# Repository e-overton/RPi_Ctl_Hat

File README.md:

Robot control pi hat
=======================

Adds buffered GPIO outputs at 5V
Adds CANbus
Adds I2C breakout pincs with protection
Adds 8-way gpio extender

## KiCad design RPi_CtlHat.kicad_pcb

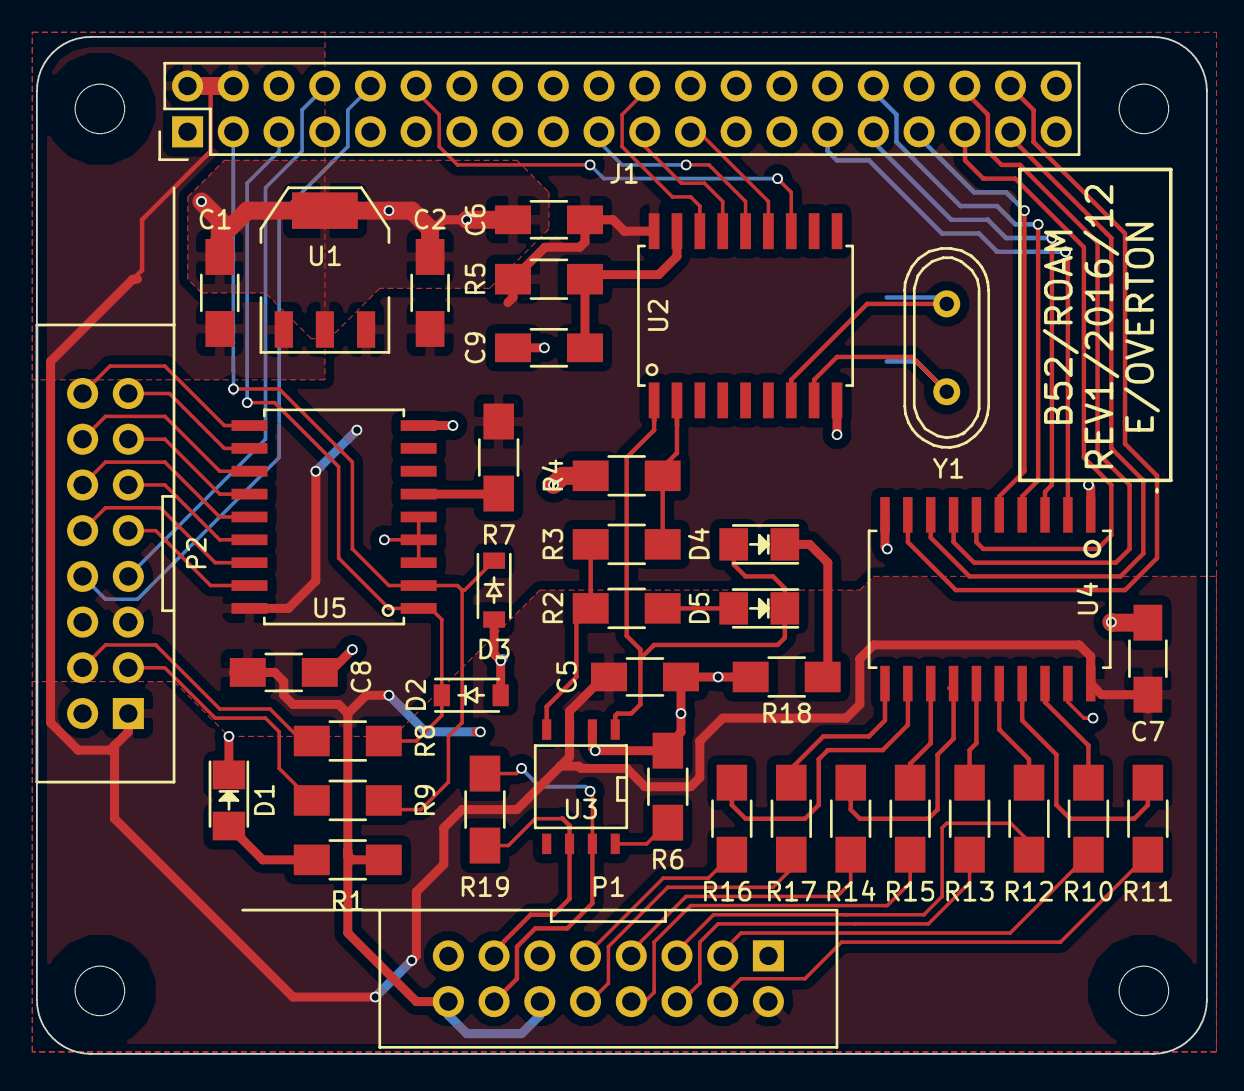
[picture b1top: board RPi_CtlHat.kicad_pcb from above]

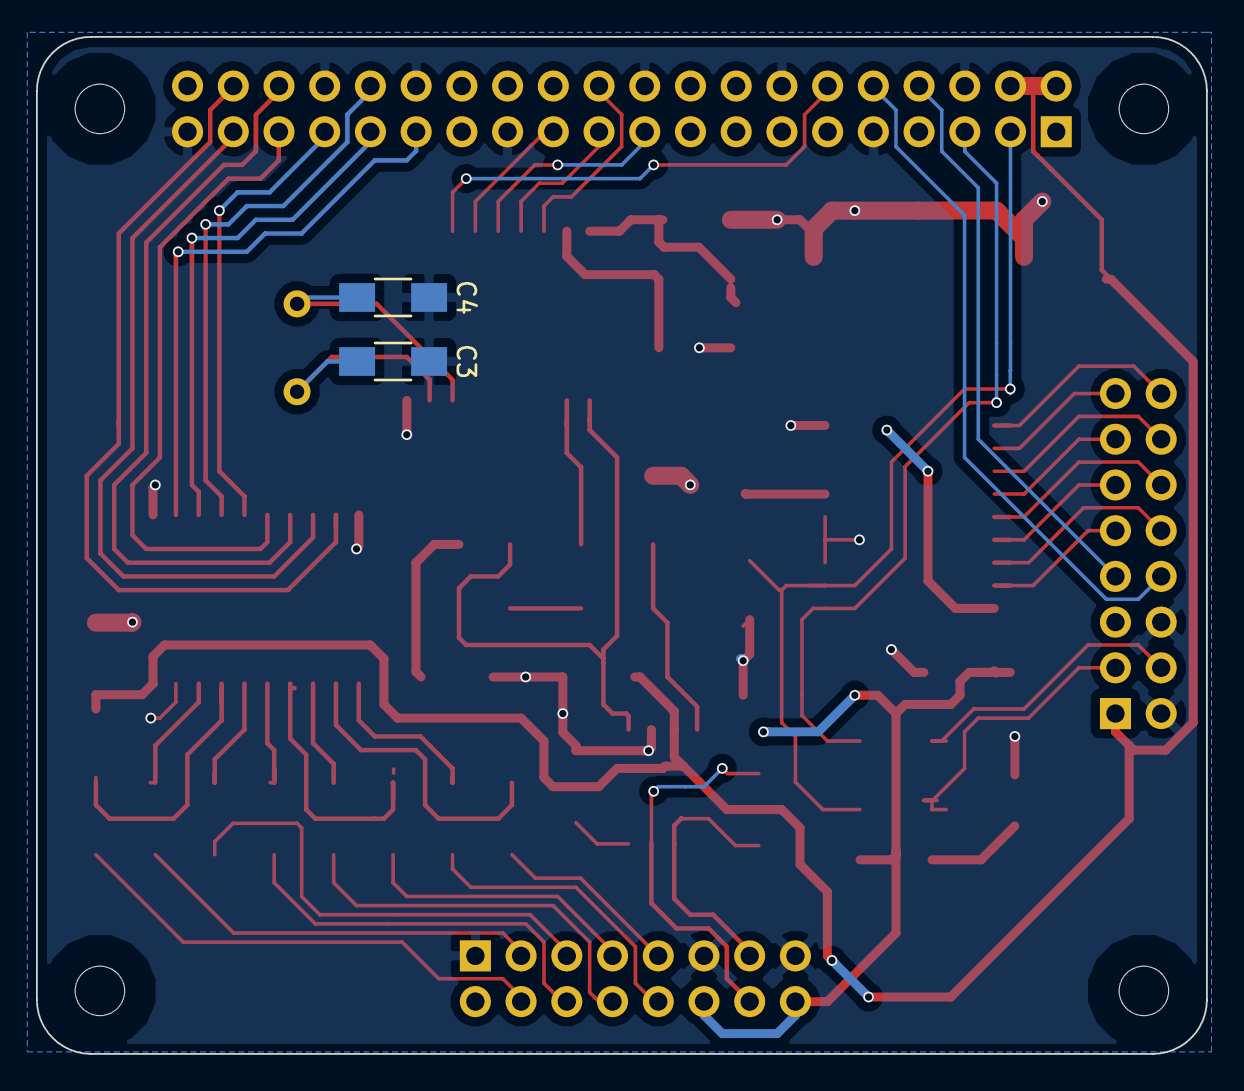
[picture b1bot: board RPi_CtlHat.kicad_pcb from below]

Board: 2 copper layers, 65.0 x 56.5 mm, 42 parts (2 on the bottom side), 59 nets.

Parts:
C1, C2: 1u; C_1206_HandSoldering
C3, C4: 22p; C_1206_HandSoldering
C5, C6, C7, C8: 100n; C_1206_HandSoldering
C9: ?n; C_1206_HandSoldering
D1, D4, D5: LED; LED_1206
D2, D3: 3.3v; SOD-123
J1: RPi_GPIO; Pin_Header_Straight_2x20
P1, P2: CONN_02X08; D300_16
R1, R8, R9, R10, R11, R12, R13, R14, R15, R16, R17: 100R; R_1206_HandSoldering
R2, R18: 200R; R_1206_HandSoldering
R3, R4, R5, R6, R7: 4k7; R_1206_HandSoldering
R19: 120R; R_1206_HandSoldering
U1: MCP1754ST-3302E/MB; SOT-223
U2: MCP2515; SOIC-18
U3: MCP2551; SOIC-8-N
U4: 74HCT541_PWR; SOIC20
U5: MCP23008; SOIC-18
Y1: 16MHz; Crystal_HC49-U_Vertical

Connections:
+5V: C1.1, C5.1, C7.1, J1.2, J1.4, P1.2, P2.1, U1.1, U3.3, U4.20
/CAN0_CE: J1.22, U2.16
/CAN0_INT: J1.12, U2.12
/CAN0_RXCAN: R3.2, R4.1, U2.2
/CAN0_TXCAN: D4.2, D5.1, U2.1, U3.1
/CANH: P1.14, R19.2, U3.7
/CANL: P1.13, R19.1, U3.6
/GPIO14TX: J1.8, P2.7
/GPIO15RX: J1.10, P2.8
/PWM0: J1.29, U4.2
/PWM0_OUT: P1.3, R10.1
/PWM1: J1.31, U4.3
/PWM1_OUT: P1.4, R11.1
/PWM2: J1.32, U4.4
/PWM2_OUT: P1.5, R12.1
/PWM3: J1.33, U4.5
/PWM3_OUT: P1.6, R13.1
/PWM4: J1.35, U4.6
/PWM4_OUT: P1.7, R14.1
/PWM5: J1.36, U4.7
/PWM5_OUT: P1.8, R15.1
/PWM6: J1.37, U4.8
/PWM6_OUT: P1.9, R16.1
/PWM7: J1.38, U4.9
/PWM7_OUT: P1.10, R17.1
/SCL1: D2.1, J1.5, R8.2, U5.1
/SCL1B: P2.4, R8.1
/SDA1: D3.1, J1.3, R9.2, U5.2
/SDA1B: P2.3, R9.1
/SPI0_CLK: J1.23, U2.13
/SPI0_MISO: J1.21, U2.15
/SPI0_MOSI: J1.19, U2.14
/XGPIO0: P2.16, U5.10
/XGPIO1: P2.15, U5.11
/XGPIO2: P2.14, U5.12
/XGPIO3: P2.13, U5.13
/XGPIO4: P2.12, U5.14
/XGPIO5: P2.11, U5.15
/XGPIO6: P2.10, U5.16
/XGPIO7: P2.9, U5.17
GND: C1.2, C2.2, C3.2, C4.2, C5.2, C6.2, C7.2, C8.2, C9.2, D1.1, D2.2, D3.2, J1.6, J1.9, J1.14, J1.20, J1.25, J1.30, J1.34, J1.39, P1.1, P1.11, P1.15, P2.2, P2.6, R4.2, R6.2, R18.1, U1.2, U1.4, U2.9, U3.2, U4.1, U4.10, U4.19, U5.3, U5.4, U5.5, U5.9
unnamed: C3.1, U2.8, Y1.2
unnamed: C4.1, U2.7, Y1.1
unnamed: C9.1, R5.2, U2.17
unnamed: D1.2, R1.2
unnamed: D4.1, R18.2
unnamed: D5.2, R2.2
unnamed: R2.1, R3.1, U3.4
unnamed: R6.1, U3.8
unnamed: R7.1, U5.6
unnamed: R10.2, U4.18
unnamed: R11.2, U4.17
unnamed: R12.2, U4.16
unnamed: R13.2, U4.15
unnamed: R14.2, U4.14
unnamed: R15.2, U4.13
unnamed: R16.2, U4.12
unnamed: R17.2, U4.11
VCC: C2.1, C6.1, C8.1, P1.12, P1.16, P2.5, R1.1, R5.1, R7.2, U1.3, U2.18, U5.18

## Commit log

2016-12-12 With 5V I2C interface
2016-12-14 First fully routed pcb
2016-12-14 First revision
2017-02-06 Added PDF Schematic
2018-05-10 Added final connector drawing for controls
